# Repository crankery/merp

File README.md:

# Merp

Modular Eurorack Powerbus (Merp) is yet another power bus [KiCad](https://www.kicad.org/) project. Yes, we're truly breaking new ground here... This has never been done before. Ahem.

## Never been done before, eh?

OK. I may have started with [Eurorack Bus Board](https://github.com/butchwarns/Eurorack_Bus_Board) by Butch Warns. I was going to just order it but it was too wide for the cheap PCB fabrications. I think I iterated on his work enough to call this its own thing.

## Why Merp?

I think the only differentator with Merp from the other power bus PCBs is that Merp is designed to be ordered from one of the Chinese PCB fabs for their minimum price. [PCBWay](https://www.pcbway.com/) for example currently has 5 boards for $5 if they're under 100mm x 100mm which Merp qualifies for.

There are 6 power bus connectors per board. If you order 5 boards you can connect them all together and have 30 x 16 pin Doepfer sockets (I hope you have at least 104 hp rails if you're doing that) 

This board rquires +12V, -12V and +5V supplies. I'm using [Meanwell RT-65](https://www.meanwell.com/webapp/product/search.aspx?prod=RT-65) to power mine. The board has no +5V conversion and performs no power regulation. If none of your Eurorack modules use +5V you can get away without it.

Use a tested power supply. Before connecting any of your Eurorack modules, power up just the bus board. Ensure the LEDs are lit. Ensure that the correct voltages present.

# Renders

Here's some pictures of the board that KiCad generated.

## Front

## Front Again

The red line on Eurorack module power connectors are to be installed towards the bottom of the board as indicated although this should be enforced by the IDC connector notches.

## Back

# Notes

- The resistor values are just a starting point. I find the +12 LED to be too bright and the +5 to be too dim with these values. They're simply there to make the power indicator LEDs a bit dimmer.
- The LEDs and the pin headers below them are the same thing. If you're connecting an LED via a header, ensure the positive leg connects to the + pin (note the pad shapes are opposite for the -12V led, the cathode is on the same side when mounted though.)
- If you don't want to use the LEDs you can leave the resistors, LEDs and associated headers unpopulated. They are not required for operation of the power bus.
- The interconnect header & socket are shown to be mounted on the back on the boards. The boards are intended to be installed in your Eurorack case on standoffs. The board should be about 5mm bigger in that dimension for this reason (it might make sense to make the whole board twice as tall to allow for staggering of the connectors as they're pretty tight)
- If you don't want to connect a module to the left or right, leave the interconnect header or socket unpopulated.
- There's an additional power header on the left side of the board. This header is entirely optional. A future revision will likely make this a screw terminal instead of a pin header.
- You can probably only populate the filter capacitors on one of your boards. Or none of them... They're optional.
- All signals are passed through all interconnected power bus modules.
- The Gate and CV lines of the Doepfer bus are connected, inclusive of module interconnects.
- The mounting holes are suitable for M3 bolts & standoffs.

# BOM

All parts are THT.

|Designator|Package|Quantity|Designation|
|-|-|-|-|
|R1|Axial Resistor 1/4W |1|12k*|
|R2,R3|Axial Resistor 1/4W|2|47k*|
|J1,J2,J3,J4,J5,J10,J11|16 Pin Eurorack Power Male|6|A,B,C,D,E,F|
|C3,C2,C1|Electrolytic Capactior|3|47uF|
|D1,D2,D3|3mm LED|1|+5V,+12V,-12V|
|J8,J9,J10|Pin Header 1x2 2.54mm Pitch Vertical|3|+5V,+12V,-12V|
|J12|Pin Connector 1x4 2.54mm Pitch|1||
|J6|Pin Socket 1x8 2.54mm Pitch Horizontal|1|IO1|
|J7|Pin Header 1x8 2.54mm Pitch Horizontal|1|IO2|

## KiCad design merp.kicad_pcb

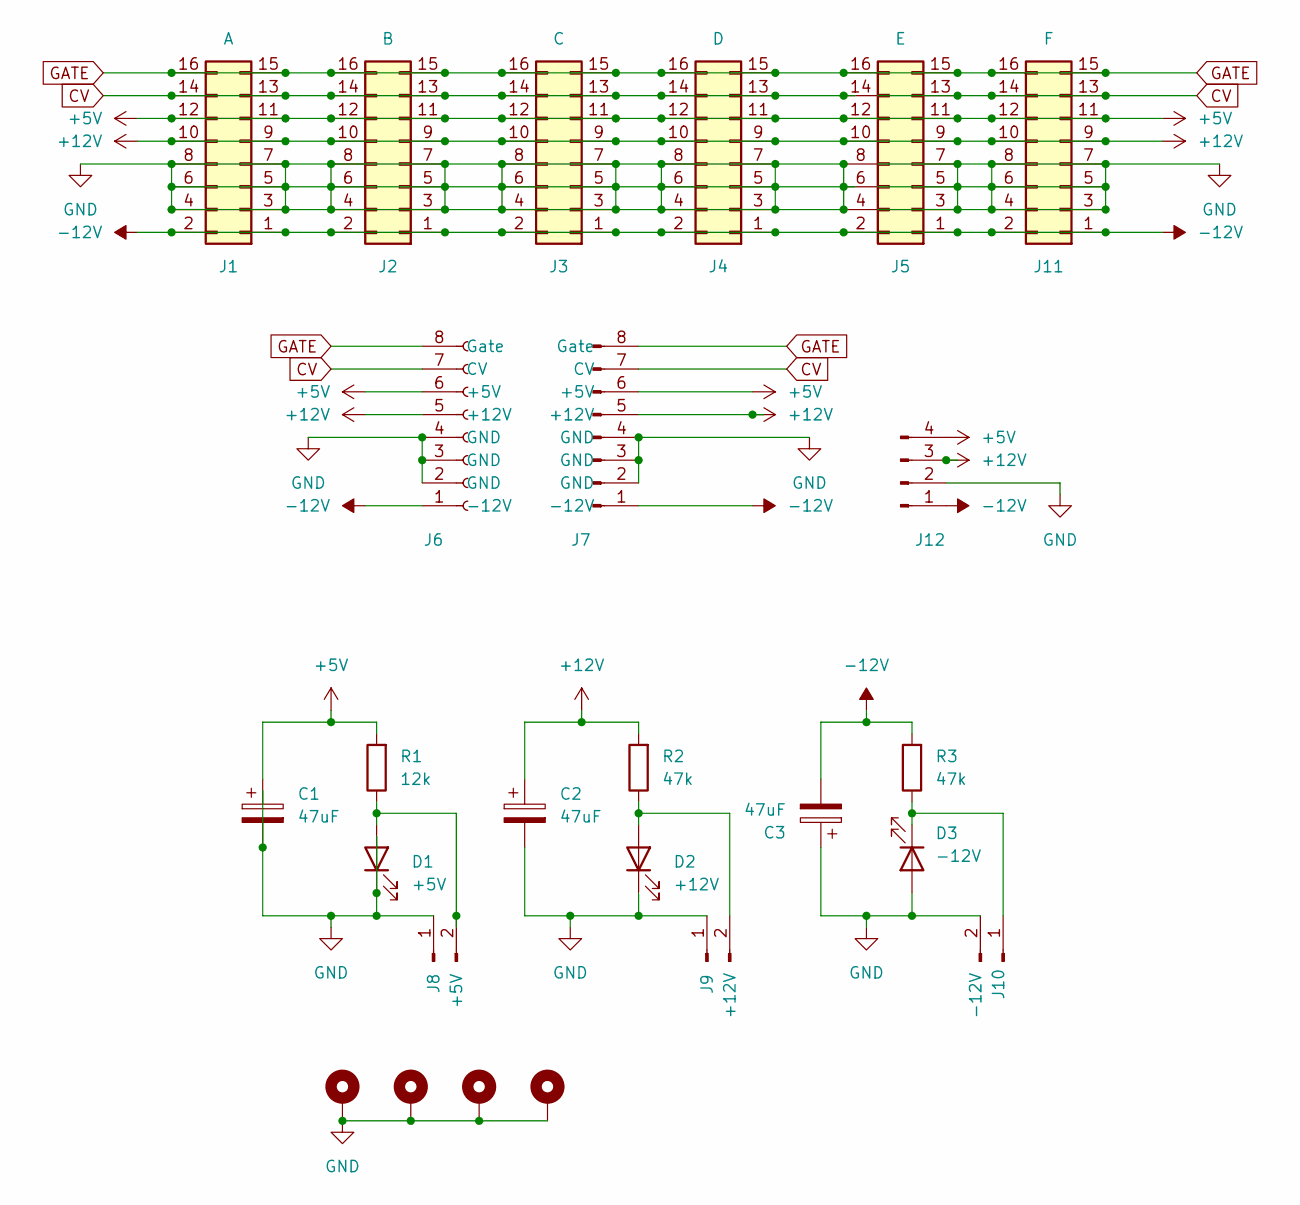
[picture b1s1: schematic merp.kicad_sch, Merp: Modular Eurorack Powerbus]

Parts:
C1, C2, C3: 47uF; CP_Radial_D8.0mm_P3.50mm
D1: +5V; LED_D3.0mm
D2: +12V; LED_D3.0mm
D3: -12V; LED_D3.0mm
H1, H2, H3, H4: GND; MountingHole_3.2mm_M3_DIN965_Pad
J1: A; IDC-Header_2x08_P2.54mm_Vertical
J2: B; IDC-Header_2x08_P2.54mm_Vertical
J3: C; IDC-Header_2x08_P2.54mm_Vertical
J4: D; IDC-Header_2x08_P2.54mm_Vertical
J5: E; IDC-Header_2x08_P2.54mm_Vertical
J6: IO1; PinSocket_1x08_P2.54mm_Horizontal
J7: IO2; PinHeader_1x08_P2.54mm_Horizontal
J8: +5V; PinHeader_1x02_P2.54mm_Vertical
J9: +12V; PinHeader_1x02_P2.54mm_Vertical
J10: -12V; PinHeader_1x02_P2.54mm_Vertical
J11: F; IDC-Header_2x08_P2.54mm_Vertical
J12: Conn_01x04_Male; PinHeader_1x04_P2.54mm_Horizontal
R1: 12k; R_Axial_DIN0207_L6.3mm_D2.5mm_P7.62mm_Horizontal
R2, R3: 47k; R_Axial_DIN0207_L6.3mm_D2.5mm_P7.62mm_Horizontal

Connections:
+5V: C1.1, J1.11, J1.12, J2.11, J2.12, J3.11, J3.12, J4.11, J4.12, J5.11, J5.12, J6.6 (+5V), J7.6 (+5V), J11.11, J11.12, J12.4, R1.2
+12V: C2.1, J1.9, J1.10, J2.9, J2.10, J3.9, J3.10, J4.9, J4.10, J5.9, J5.10, J6.5 (+12V), J7.5 (+12V), J11.9, J11.10, J12.3, R2.2
-12V: C3.2, J1.1, J1.2, J2.1, J2.2, J3.1, J3.2, J4.1, J4.2, J5.1, J5.2, J6.1 (-12V), J7.1 (-12V), J11.1, J11.2, J12.1, R3.2
CV: J1.13, J1.14, J2.13, J2.14, J3.13, J3.14, J4.13, J4.14, J5.13, J5.14, J6.7 (CV), J7.7 (CV), J11.13, J11.14
GATE: J1.15, J1.16, J2.15, J2.16, J3.15, J3.16, J4.15, J4.16, J5.15, J5.16, J6.8 (Gate), J7.8 (Gate), J11.15, J11.16
GND: C1.2, C2.2, C3.1, D1.1 (K), D2.1 (K), D3.2 (A), H1.1, H2.1, H3.1, H4.1, J1.3, J1.4, J1.5, J1.6, J1.7, J1.8, J2.3, J2.4, J2.5, J2.6, J2.7, J2.8, J3.3, J3.4, J3.5, J3.6, J3.7, J3.8, J4.3, J4.4, J4.5, J4.6, J4.7, J4.8, J5.3, J5.4, J5.5, J5.6, J5.7, J5.8, J6.2 (GND), J6.3 (GND), J6.4 (GND), J7.2 (GND), J7.3 (GND), J7.4 (GND), J8.1, J9.1, J10.2, J11.3, J11.4, J11.5, J11.6, J11.7, J11.8, J12.2
unnamed: D1.2 (A), J8.2, R1.1
unnamed: D2.2 (A), J9.2, R2.1
unnamed: D3.1 (K), J10.1, R3.1

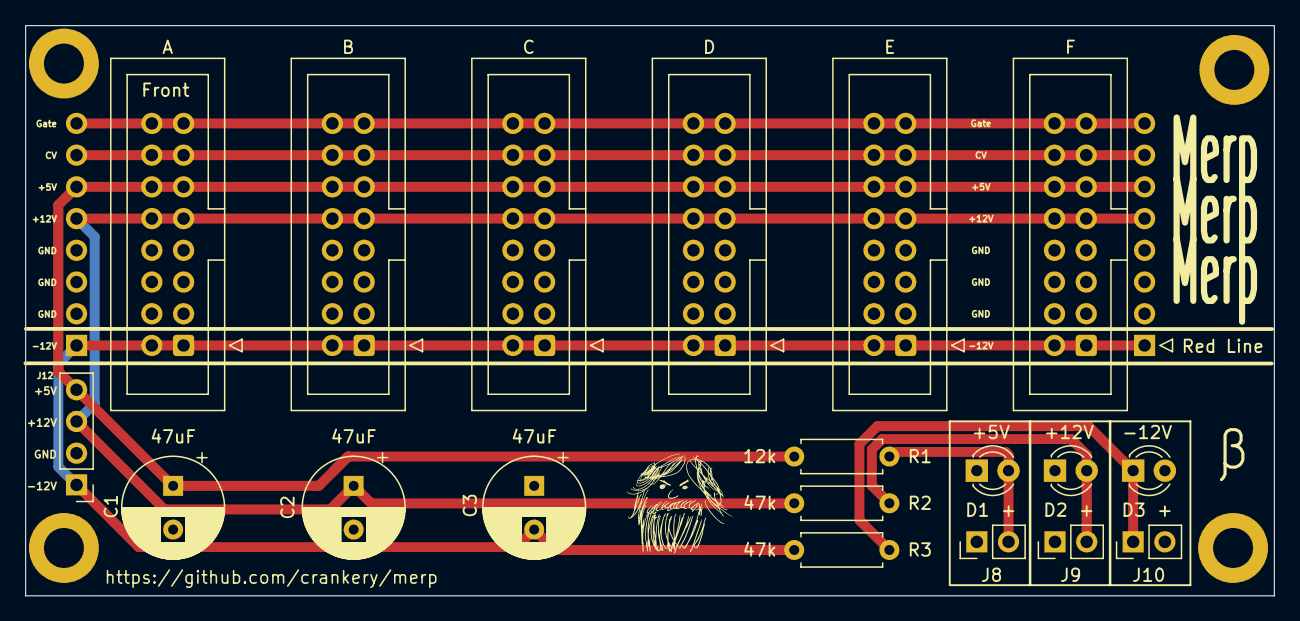
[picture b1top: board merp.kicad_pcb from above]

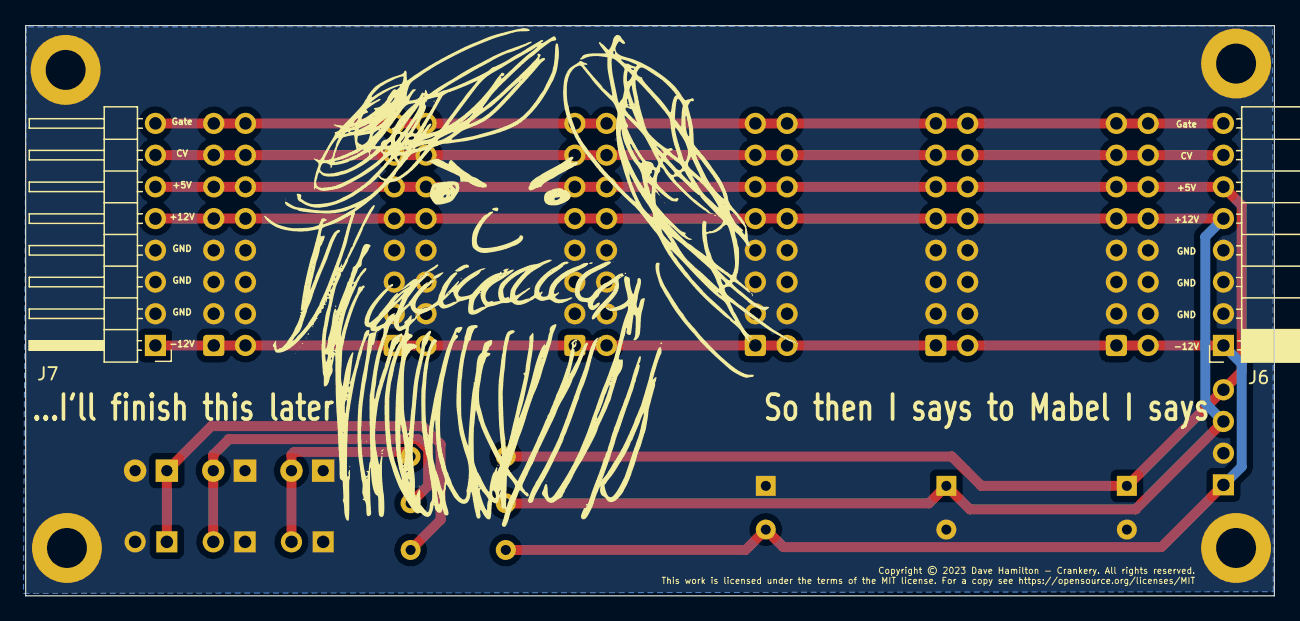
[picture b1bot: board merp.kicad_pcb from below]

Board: 2 copper layers, 100.0 x 45.7 mm, 26 parts (2 on the bottom side), 9 nets.

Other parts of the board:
G1: LOGO; crankery_small

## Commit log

2023-07-04 Update LICENSE
2023-07-04 add project to source control
2023-07-04 Update fp-lib-table
2023-07-04 cleanup
2023-07-04 Add macos stuff to git ignore
2023-07-04 remove junk
2023-07-04 maybe i want to save xml or cvs files.
2023-07-04 add gerbers
2023-07-04 add BOM
2023-07-04 typo typo typo
2023-07-04 fix url on board
    upgrade to kicad 7
2023-07-04 update gerbers and front images
2023-07-04 bigger sample images
2023-07-04 more churn
2023-07-28 remove pessimistic note about mounting holes. they're fine.

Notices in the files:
merp.kicad_pcb:
Copyright © 2023 Dave Hamilton - Crankery. All rights reserved.
This work is licensed under the terms of the MIT license. For a copy see https://opensource.org/licenses/MIT
